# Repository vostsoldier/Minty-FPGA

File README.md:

# Minty - A ECP5 based devboard with DDR3 RAM
## An introduction
Hey fellas it's Technical here with a cool beans board!!!
I wanted to experiment with FPGAs and RAM at the same time, so I thought, why not just combine the two onto one board!
What a great idea right!!! Hahahahahahhahaha!
But yeah thats how this board came to be...
At the time of writing (10/5/25), the board only has a few key parts needed for it to function..
HOWEVER, I am planning to put more cool stuff onto it, as I have like 150 IO pins left lol...
Feel free to DM technical_. on the Hack Club slack if you have any ideas for what to put!!!

## Features (As of 10/5/25)
- Lattice ECP5 FPGA
  * 44k LUTS
  * 1944 KiB of Embedded Memory
  * 351 KiB of RAM
- DDR3 RAM
  * 2GB
  * DDR3??
- 100 Mhz clock (probably)
- Snazzy Name

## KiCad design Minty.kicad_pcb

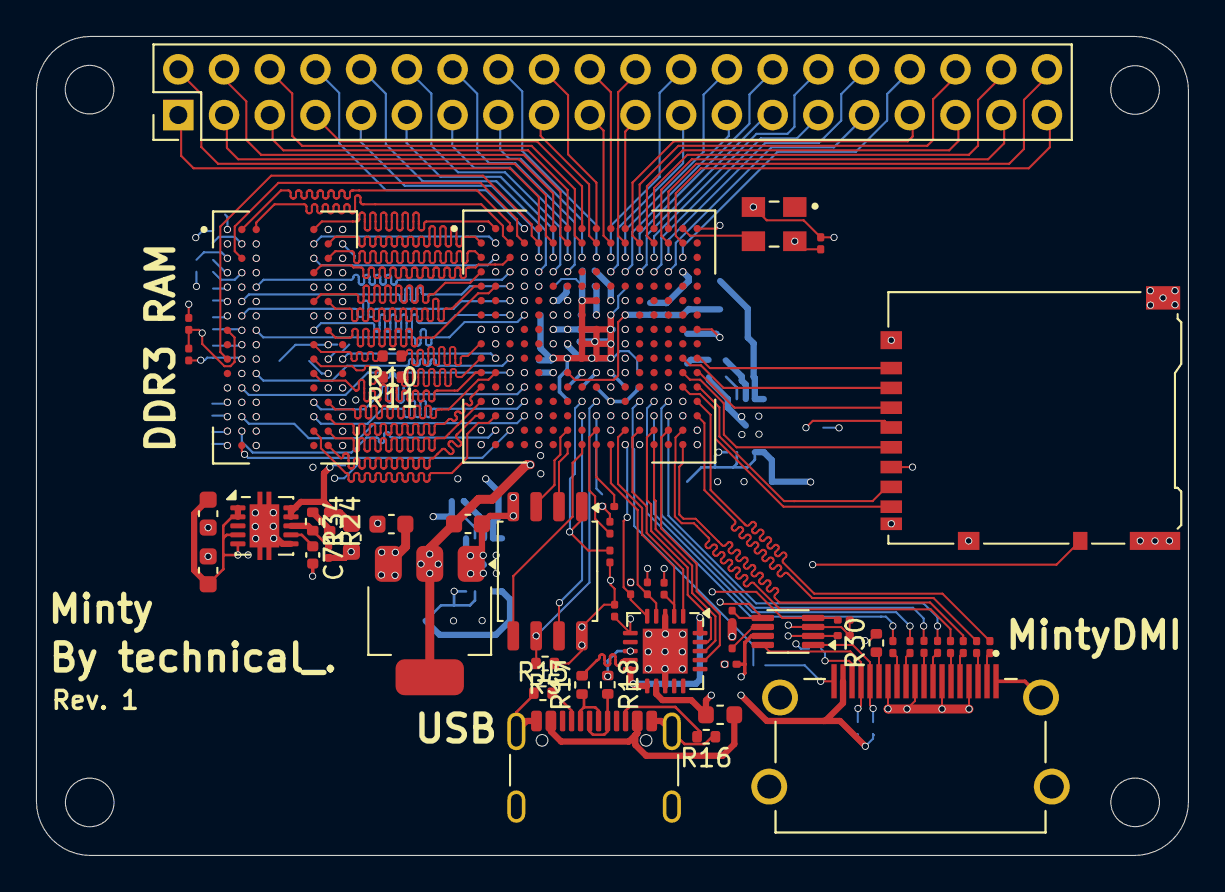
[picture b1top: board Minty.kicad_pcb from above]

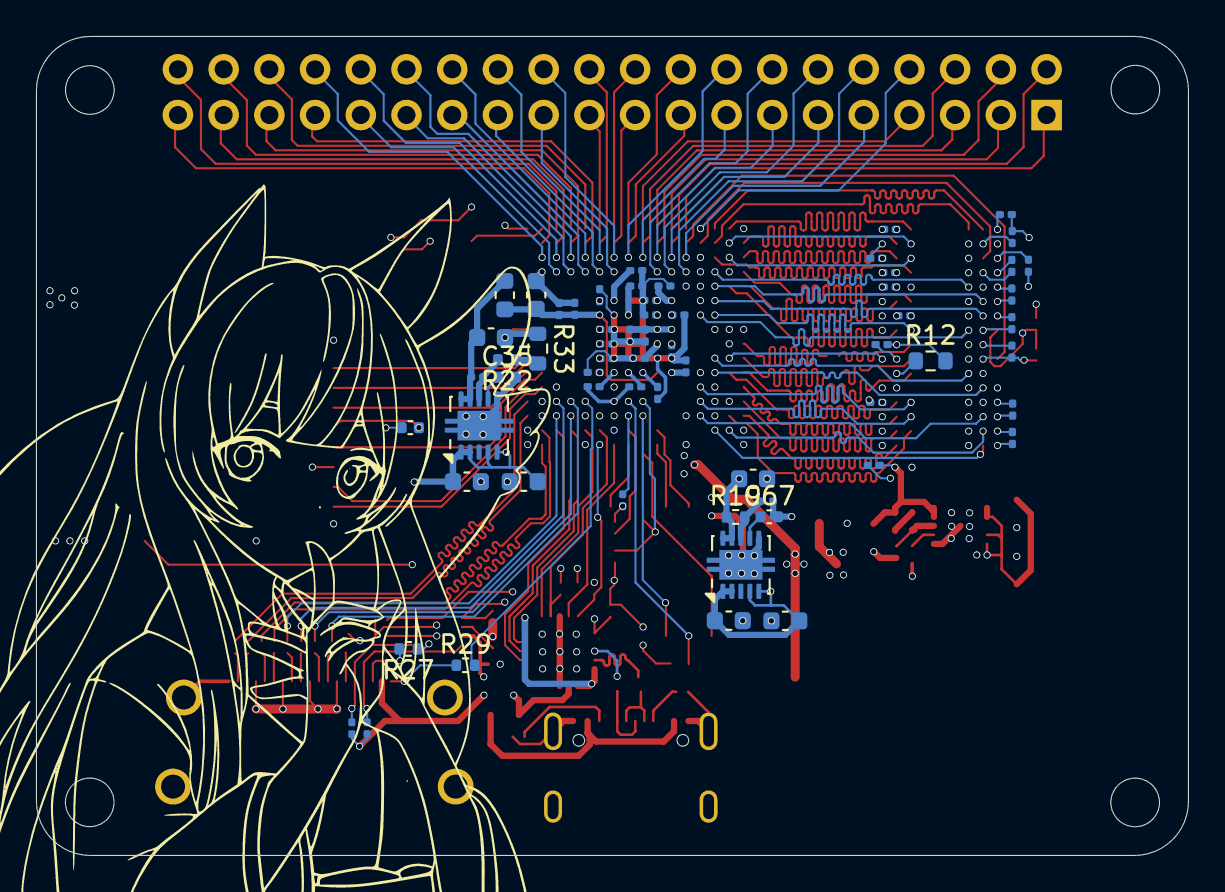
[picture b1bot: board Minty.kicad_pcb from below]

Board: 6 copper layers, 64.0 x 45.5 mm, 119 parts (62 on the bottom side), 165 nets.

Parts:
C4, C5, C6, C7, C8, C9, C11, C12, C14, C15, C17, C18, C20, C21, C23, C24, C26, C27, C29, C30, C32, C42, C45, C46, C47, C48, C49, C53, C55, C56, C57, C58, C59, C60, C61, C62, C63, C64, C72, C81, C82: 100n; C_0201_0603Metric
C10, C33, C38, C66, C70: 10u; C_0603_1608Metric
C34: 22u; C_0603_1608Metric
C35, C67, C71: 1n; C_0402_1005Metric
C36, C37, C39, C40, C68, C69: 1u; C_0603_1608Metric
C65: 10u; C_0402_1005Metric
C73, C74, C75, C76, C77, C78, C79, C80: 22n; C_0201_0603Metric
F1: Fuse; Fuse_0603_1608Metric
FB1: 120 | 100MHz; L_0603_1608Metric
H1, H2, H3, H4: MountingHole; MountingHole_2.7mm_M2.5
J1: USB_C_Receptacle_USB2.0_16P; USB_C_Receptacle_GCT_USB4105-xx-A_16P_TopMnt_Horizontal
J2: Micro_SD_Card_Det_Hirose_DM3AT; microSD_HC_Hirose_DM3AT-SF-PEJM5
J3: Conn_02x20_Counter_Clockwise; PinHeader_2x20_P2.54mm_Vertical
J4: HDMI_C_1.4; AMPHENOL_10029449-111RLF
R1, R2, R3, R4, R6, R7, R8, R9, R13, R14, R20, R21, R23, R25, R26, R28, R31, R32: 4k7; R_0201_0603Metric
R5: 1k; R_0402_1005Metric
R10, R11, R17, R18: 33; R_0402_1005Metric
R12, R33: 240; R_0603_1608Metric
R15, R16: 5k1; R_0402_1005Metric
R19, R22, R24, R34: 2k; R_0402_1005Metric
R27: 10k; R_0402_1005Metric
R29, R30: 470; R_0402_1005Metric
U1: LFE5U-45F-7BG256I; BGA256C80P16X16_1400X1400X170
U2: AMS1117-3.3; SOT-223-3_TabPin2
U3: TXS0102DCU; VSSOP-8_2.3x2mm_P0.5mm
U5: W25Q128JVS; SOIC-8_5.3x5.3mm_P1.27mm
U6: MT41J128M16JT-125_KTR; BGA96C80P6X16_800X1400X120
U8: FT231XQ; QFN-20-1EP_4x4mm_P0.5mm_EP2.5x2.5mm
U9, U10, U11: TPS74801DRC; VSON-10-1EP_3x3mm_P0.5mm_EP1.65x2.4mm_ThermalVias
Y1: ECS-3225MVQ-1000-CN-TR; OSC_ECS-3225MVQ-1000-CN-TR

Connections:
+1.1V: C4.1, C5.1, C6.1, C7.1, C8.1, C9.1, C66.1, R19.1, U1.G6 (VCC), U1.G7 (VCC__1), U1.G9 (VCC__2), U1.L8 (VCC__3), U1.L9 (VCC__4), U1.L10 (VCC__5), U9.9 (OUT), U9.10 (OUT)
+1.5V: C42.1, C45.1, C46.1, C47.1, C48.1, C49.1, C53.1, C55.1, C56.1, C57.1, C58.1, C59.1, C60.1, C61.1, C62.1, C63.1, C64.1, C70.1, R13.1, R24.1, U6.A1 (VDDQ), U6.A8 (VDDQ__1), U6.B2 (VDD), U6.C1 (VDDQ__2), U6.C9 (VDDQ__3), U6.D2 (VDDQ__4), U6.D9 (VDD__1), U6.E9 (VDDQ__5), U6.F1 (VDDQ__6), U6.G7 (VDD__2), U6.H2 (VDDQ__7), U6.H9 (VDDQ__8), U6.K2 (VDD__3), U6.K8 (VDD__4), U6.N1 (VDD__5), U6.N9 (VDD__6), U6.R1 (VDD__7), U6.R9 (VDD__8), U11.9 (OUT), U11.10 (OUT)
+2.5V: C38.1, FB1.1, R21.2, U10.9 (OUT), U10.10 (OUT)
+3.3V: C14.1, C15.1, C17.1, C18.1, C20.1, C21.1, C23.1, C24.1, C26.1, C27.1, C29.1, C30.1, C32.1, C34.1, C65.2, C72.1, C81.1, J2.4 (VDD), R1.1, R2.1, R3.1, R5.1, R6.1, R7.1, R8.1, R9.1, R25.1, R26.1, R28.1, U1.F6 (VCCIO0), U1.F7 (VCCIO0__1), U1.F10 (VCCIO1), U1.F11 (VCCIO1__1), U1.H6 (VCCIO7), U1.H7 (VCCIO7__1), U1.H11 (VCCIO2), U1.J6 (VCCIO6), U1.J7 (VCCIO6__1), U1.J11 (VCCIO2__1), U1.K11 (VCCIO3), U1.L6 (VCCIO8), U1.L11 (VCCIO3__1), U2.2 (VO), U3.3 (VCCA), U5.8 (VCC), Y1.4 (VDD)
+5V: C33.1, C36.1, C37.2, C39.2, C40.1, C68.2, C69.1, C82.1, F1.2, J4.18 (+5V), R31.1, R32.1, U2.3 (VI), U3.7 (VCCB), U8.12 (VCC), U9.1 (IN), U9.2 (IN), U9.4 (BIAS), U9.5 (EN), U10.1 (IN), U10.2 (IN), U10.4 (BIAS), U10.5 (EN), U11.1 (IN), U11.2 (IN), U11.4 (BIAS), U11.5 (EN)
/A0: U1.M3 (PL41D), U6.N3 (A0)
/A1: U1.N4 (PL59A), U6.P7 (A1)
/A2: U1.P3 (PL59B), U6.P3 (A2)
/A3: U1.N3 (PL44D), U6.N2 (A3)
/A4: U1.M1 (PL35C), U6.P8 (A4)
/A5: U1.P4 (PL62A), U6.P2 (A5)
/A6: U1.N1 (PL41A), U6.R8 (A6)
/A7: U1.R2 (PL59C), U6.R2 (A7)
/A8: U1.P1 (PL44A), U6.T8 (A8)
/A9: U1.R1 (PL44B), U6.R3 (A9)
/A10: U1.L1 (PL35A), U6.L7 (A10/AP)
/A11: U1.P2 (PL41B), U6.R7 (A11)
/A12: U1.M4 (PL44C), U6.N7 (A12/~BC)
/A13: U1.P5 (PL68D), U6.T3 (A13)
/BA0: U1.L3 (PL41C), U6.M2 (BA0)
/BA1: U1.L2 (PL35B), U6.N8 (BA1)
/BA2: U1.L4 (PL38C), U6.M3 (BA2)
/CAS: U1.H3 (PL23D), U6.K3 (~CAS)
/CK+: R10.2, U6.J7 (CK)
/CK-: R11.2, U6.K7 (~CK)
/CKE: U1.K2 (PL32D), U6.K9 (CKE)
/CS: U1.J2 (PL32B), U6.L2 (~CS)
/DQ0: U1.D3 (PL11D), U6.E3 (DQ0)
/DQ1: U1.D1 (PL17A), U6.F7 (DQ1)
/DQ2: U1.E3 (PL14C), U6.F2 (DQ2)
/DQ3: U1.E1 (PL20D), U6.F8 (DQ3)
/DQ4: U1.G4 (PL20B), U6.H3 (DQ4)
/DQ5: U1.E2 (PL17B), U6.H8 (DQ5)
/DQ6: U1.F3 (PL14D), U6.G2 (DQ6)
/DQ7: U1.G3 (PL23C), U6.H7 (DQ7)
/DQ8: U1.C3 (PL11C), U6.D7 (DQ8)
/DQ9: U1.C4 (PT11A), U6.C3 (DQ9)
/DQ10: U1.C1 (PL14A), U6.C8 (DQ10)
/DQ11: U1.B4 (PT11B), U6.C2 (DQ11)
/DQ12: U1.A2 (PT4A), U6.A7 (DQ12)
/DQ13: U1.A3 (PT6A), U6.A2 (DQ13)
/DQ14: U1.B1 (PL11A), U6.B8 (DQ14)
/DQ15: U1.B3 (PT4B), U6.A3 (DQ15)
/Filtered 2.5V: C10.1, C11.1, C12.1, FB1.2, U1.G11 (VCCAUX), U1.L7 (VCCAUX__1)
/Flash_CLK: R5.2, U1.N9 (CCLK), U5.6 (CLK)
/Flash_CS: R7.2, U1.N8 (PB15A), U5.1 (~CS)
/Flash_MISO: U1.T7 (PB11A), U5.2 (DO/IO_{1})
/Flash_MOSI: U1.T8 (PB11B), U5.5 (DI/IO_{0})
/Flash_RESET: U1.P8 (PB13B), U5.7 (~HOLD/~RESET/IO_{3})
/Flash_WP: U1.R7 (PB6A), U5.3 (~WP/IO_{2})
/HDMI_CEC: R30.2, U1.R16 (PR44B)
/HDMI_CLK+: C79.2, U1.P13 (PR62A)
/HDMI_CLK-: C80.2, U1.N13 (PR59A)
/HDMI_D0+: C77.2, U1.P14 (PR59B)
/HDMI_D0-: C78.2, U1.N14 (PR44D)
/HDMI_D1+: C75.2, U1.T15 (PR59D)
/HDMI_D1-: C76.2, U1.R15 (PR59C)
/HDMI_D2+: C73.2, U1.N16 (PR41A)
/HDMI_D2-: C74.2, U1.P16 (PR44A)
/HDMI_HPD: R29.2, U1.N12 (PR65D)
/HDMI_SCL_3V3: R25.2, U1.P11 (PR68C), U3.5 (A1)
/HDMI_SCL_5V: J4.15 (SCL), R31.2, U3.1 (B2)
/HDMI_SDA_3V3: R26.2, U1.P12 (PR68D), U3.4 (A2)
/HDMI_SDA_5V: J4.16 (SDA), R32.2, U3.8 (B1)
/HDMI_UTIL: R27.1, U1.P15 (PR41B)
/Header_1: J3.1, U1.A5 (PT18A)
/Header_2: J3.2, U1.B6 (PT31B)
/Header_3: J3.3, U1.A6 (PT18B)
/Header_4: J3.4, U1.B7 (PT36B)
/Header_5: J3.5, U1.A7 (PT38A)
/Header_6: J3.6, U1.B8 (PT44B)
/Header_7: J3.7, U1.A8 (PT38B)
/Header_8: J3.8, U1.A4 (PT6B)
/Header_9: J3.9, U1.C5 (PT15A)
/Header_10: J3.10, U1.D5 (PT13B)
/Header_11: J3.11, U1.C6 (PT31A)
/Header_12: J3.12, U1.D6 (PT20B)
/Header_13: J3.13, U1.C7 (PT36A)
/Header_14: J3.14, U1.D7 (PT33B)
/Header_15: J3.15, U1.C8 (PT44A)
/Header_16: J3.16, U1.C9 (PT47B)
/Header_17: J3.17, U1.B9 (PT47A)
/Header_18: J3.18, U1.A9 (PT51A)
/Header_19: J3.19, U1.B10 (PT53A)
/Header_20: J3.20, U1.A10 (PT51B)
/Header_21: J3.21, U1.A11 (PT71A)
/Header_22: J3.22, U1.B11 (PT58A)
/Header_23: J3.23, U1.D10 (PT56A)
/Header_24: J3.24, U1.C10 (PT53B)
/Header_25: J3.25, U1.D11 (PT69A)
/Header_26: J3.26, U1.C11 (PT58B)
/Header_27: J3.27, U1.D12 (PT76A)
/Header_28: J3.28, U1.C12 (PT74B)
/Header_29: J3.29, U1.D13 (PT80A)
/Header_30: J3.30, U1.C13 (PT78B)
/Header_31: J3.31, U1.D14 (PR11D)
/Header_32: J3.32, U1.C14 (PR11C)
/Header_33: J3.33, U1.B12 (PT74A)
/Header_34: J3.34, U1.C15 (PR14B)
/Header_35: J3.35, U1.B13 (PT78A)
/Header_36: J3.36, U1.A12 (PT71B)
/Header_37: J3.37, U1.B14 (PT85A)
/Header_38: J3.38, U1.A13 (PT83A)
/Header_39: J3.39, U1.B15 (PR11B)
/Header_40: J3.40, U1.A14 (PT83B)
/LDM: U1.E5 (PT13A), U6.E7 (LDM)
/LDQS+: U1.E4 (PT9A), U6.F3 (LDQS)
/LDQS-: U1.F4 (PL17C), U6.G3 (~LDQS)
/ODT: U1.B5 (PT15B), U6.K1 (ODT)
/OSC OUT: U1.A15 (PT85B), Y1.3 (OUTPUT)
/PROGRAM: R6.2, U1.R9 (~PROGRAM)
/RAS: U1.H2 (PL29B), U6.J3 (~RAS)
/RESET: U1.R3 (PL62B), U6.T2 (~RESET)
/SD_CLK: J2.5 (CLK), U1.L15 (PR35B)
/SD_CMD: J2.3 (CMD), U1.L16 (PR35A)
/SD_DAT0: J2.7 (DAT0), U1.M16 (PR35C)
/SD_DAT1: J2.8 (DAT1), U1.M15 (PR35D)
/SD_DAT2: J2.1 (DAT2), U1.K16 (PR32C)
/SD_DAT3: J2.2 (DAT3/CD), U1.K15 (PR32D)
/SD_DET: J2.10 (DET_A), U1.M14 (PR41D)
/TCK: R4.1, U1.T10 (TCK), U8.4 (~DSR)
/TDI: R2.2, U1.R11 (TDI), U8.2 (~RI)
/TDO: R3.2, U1.M10 (TDO), U8.6 (~CTS)
/TMS: R1.2, U1.T11 (TMS), U8.5 (~DCD)
/UDM: U1.D4 (PT9B), U6.D3 (UDM)
/UDQS+: U1.C2 (PL14B), U6.C7 (UDQS)
/UDQS-: U1.B2 (PL11B), U6.B7 (~UDQS)
/USB_DTR: U1.T13 (PR65B), U8.18 (~DTR)
/USB_RTS: U1.R13 (PR62C), U8.19 (~RTS)
/USB_RX: U1.R12 (PR65A), U8.1 (RXD)
/USB_TX: U1.R14 (PR62B), U8.17 (TXD)
/WE: U1.K3 (PL29D), U6.L3 (~WE)
GND: C4.2, C5.2, C6.2, C7.2, C8.2, C9.2, C10.2, C11.2, C12.2, C14.2, C15.2, C17.2, C18.2, C20.2, C21.2, C23.2, C24.2, C26.2, C27.2, C29.2, C30.2, C32.2, C33.2, C34.2, C35.2, C36.2, C37.1, C38.2, C39.1, C40.2, C42.2, C45.2, C46.2, C47.2, C48.2, C49.2, C53.2, C55.2, C56.2, C57.2, C58.2, C59.2, C60.2, C61.2, C62.2, C63.2, C64.2, C65.1, C66.2, C67.2, C68.1, C69.2, C70.2, C71.2, C72.2, C81.2, C82.2, J1.A1 (GND), J1.B1 (GND), J1.S1 (SHIELD), J2.6 (VSS), J2.9 (DET_B), J2.11 (SHIELD), J4.1 (D2S), J4.4 (D1S), J4.7 (D0S), J4.10 (CKS), J4.13 (GND), R4.2, R12.2, R14.2, R15.1, R16.1, R20.2, R23.2, R33.1, U1.A1 (GND1), U1.A16 (GND1__1), U1.D2 (GND1__2), U1.D15 (GND1__3), U1.F8 (GND1__4), U1.F9 (GND1__5), U1.G8 (GND1__6), U1.G10 (GND1__7), U1.H1 (GND1__8), U1.H8 (GND1__9), U1.H9 (GND1__10), U1.H10 (GND1__11), U1.H16 (GND1__12), U1.J8 (GND2), U1.J9 (GND2__1), U1.J10 (GND2__2), U1.K6 (GND2__3), U1.K7 (GND2__4), U1.K8 (GND2__5), U1.K9 (GND2__6), U1.K10 (GND2__7), U1.N2 (GND2__8), U1.N10 (CFG_0), U1.N15 (GND2__9), U1.P10 (CFG_1), U1.R10 (CFG_2), U1.T1 (GND2__10), U1.T5 (GND2__11), U1.T12 (GND2__12), U1.T16 (GND2__13), U2.1 (GND), U3.2 (GND), U5.4 (GND), U6.A9 (VSS), U6.B1 (VSSQ), U6.B3 (VSS__1), U6.B9 (VSSQ__1), U6.D1 (VSSQ__2), U6.D8 (VSSQ__3), U6.E1 (VSS__2), U6.E2 (VSSQ__4), U6.E8 (VSSQ__5), U6.F9 (VSSQ__6), U6.G1 (VSSQ__7), U6.G8 (VSS__3), U6.G9 (VSSQ__8), U6.J2 (VSS__4), U6.J8 (VSS__5), U6.M1 (VSS__6), U6.M9 (VSS__7), U6.P1 (VSS__8), U6.P9 (VSS__9), U6.T1 (VSS__10), U6.T9 (VSS__11), U8.3 (GND), U8.13 (GND), U8.21 (GND), U9.6 (GND), U9.11 (GND), U10.6 (GND), U10.11 (GND), U11.6 (GND), U11.11 (GND), Y1.2 (GND)
unnamed: F1.1, J1.A4 (VBUS), J1.B4 (VBUS)
unnamed: J1.A5 (CC1), R15.2
unnamed: J1.B5 (CC2), R16.2
unnamed: J1.A6 (D+), J1.B6 (D+), R18.2
unnamed: J1.A7 (D-), J1.B7 (D-), R17.1
unnamed: J4.14 (CEC), R30.1
unnamed: C79.1, J4.11 (CK+)
unnamed: C80.1, J4.12 (CK-)
unnamed: C77.1, J4.8 (D0+)
unnamed: C78.1, J4.9 (D0-)
unnamed: C75.1, J4.5 (D1+)
unnamed: C76.1, J4.6 (D1-)
unnamed: C73.1, J4.2 (D2+)
unnamed: C74.1, J4.3 (D2-)
unnamed: J4.19 (HPD/HEAC-), R29.1
unnamed: J4.17 (UTILITY/HEAC+), R27.2
unnamed: R22.1, R33.2
unnamed: R24.2, R34.1
unnamed: R10.1, U1.J1 (PL32A)
unnamed: R11.1, U1.K1 (PL32C)
unnamed: R8.2, U1.P9 (DONE)
unnamed: R9.2, U1.T9 (~INIT)
unnamed: R28.2, U3.6 (OE)
unnamed: R13.2, R14.1, U6.H1 (VREFDQ), U6.M8 (VREFCA)
unnamed: R12.1, U6.L8 (ZQ)
unnamed: R17.2, R18.1, U8.8 (USBDP), U8.9 (USBDM), U8.10 (3V3OUT), U8.11 (~RESET), U8.20 (VCCIO)
unnamed: R19.2, R20.1, U9.8 (FB)
unnamed: C67.1, U9.7 (SS)
unnamed: R21.1, R22.2, U10.8 (FB)
unnamed: C35.1, U10.7 (SS)
unnamed: R23.1, R34.2, U11.8 (FB)
unnamed: C71.1, U11.7 (SS)

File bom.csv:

Id,Designator,Footprint,Quantity,Designation,LCSC #,Price/unit,Total Price
1,"C35, C67, C71",0402_1005,3,1n,C1523,0.0011,1.5033
2,"C73, C74, C75, C76, C77, C78, C79, C80",0201_0603,8,22n,C161473,0.0076,1.5608
3,"C4, C5, C6, C7, C8, C9, C11, C12, C14, C15, C17, C18, C20, C21, C23, C24, C26, C27, C29, C30, C32, C42, C45, C46, C47, C48, C49, C53, C54, C55, C56, C57, C58, C59, C60, C61, C62, C63, C64, C72, C81, C82",0201_0603,41,100n,C49062,0.0013,1.5533
4,"C36, C37, C39, C40, C68, C69",0603_1608,6,1u,C15849,0.0047,1.5282
5,C65,0402_1005,1,10u,C15525,0.005,1.505
6,"C10, C33, C38, C66, C70",0603_1608,5,10u,C19702,0.0056,1.528
7,C34,0603_1608,1,22u,C59461,0.0086,1.5086
8,"R10, R11, R17, R18",0402_1005,4,33,C25105,0.0006,1.5024
9,"R12, R33",0603_1608,2,240,C23350,0.0007,1.5014
10,"R29, R30",0402_1005,2,470,C17710,0.0018,1.5036
11,R5,0402_1005,1,1k,C11702,0.0005,1.5005
12,"R19, R22, R24, R34, ",0402_1005,4,2k,C4109,0.0005,1.502
13,"R1, R2, R3, R4, R6, R7, R8, R9, R13, R14, R20, R21, R23, R25, R26, R28, R31, R32",0201_0603,18,4k7,C138135,0.0008,1.5144
14,"R15, R16",0402_1005,2,5k1,C11702,0.0005,1.501
15,R27,0402_1005,1,10k,C25744,0.0005,1.5005
16,FB1,0603_1608,1,120 | 100MHz,C14709,0.0064,1.5064
17,F1,0603_1608,1,Fuse,C210357,0.0347,1.5347
18,"U9, U10, U11",VSON-10-1EP_3x3mm_P0.5mm_EP1.65x2.4mm_ThermalVias,3,TPS74801DRC,C105263,0.2225,2.1675
19,U2,SOT-223-3_TabPin2,1,AMS1117-3.3,C6186,0.1622,1.6622
20,U5,SOIC-8_5.3x5.3mm_P1.27mm,1,W25Q128JVS,C97521,1.0605,2.5605
21,U8,QFN-20-1EP_4x4mm_P0.5mm_EP2.5x2.5mm,1,FT231XQ,C132159,4.503,6.003
22,U3,VSSOP-8_2.3x2mm_P0.5mm,1,TXS0102DCU,C53434,0.1266,1.6266
23,Y1,OSC_ECS-3225MVQ-1000-CN-TR,1,ECS-3225MVQ-1000-CN-TR,C2595933,2.217,3.717
24,U1,BGA256C80P16X16_1400X1400X170,1,LFE5U-45F-7BG256I,C1550826,15.8235,17.3235
25,U6,BGA96C80P6X16_800X1400X120,1,MT41J128M16JT-125_KTR,C426885,3.36,4.86
26,J1,USB_C_Receptacle_GCT_USB4105-xx-A_16P_TopMnt_Horizontal,1,USB_C_Receptacle_USB2.0_16P,C2765186,0.0563,1.5563
27,J2,microSD_HC_Hirose_DM3AT-SF-PEJM5,1,Micro_SD_Card_Det_Hirose_DM3AT,C114218,1.203,2.703
28,J4,AMPHENOL_10029449-11RLF,1,HDMI_C_1.4,C427307,,139.8674

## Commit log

2025-10-06 Create README for Minty ECP5 devboard project
    Added initial README with project introduction and features.
2025-10-10 finished
2025-10-10 blueprint reqs
